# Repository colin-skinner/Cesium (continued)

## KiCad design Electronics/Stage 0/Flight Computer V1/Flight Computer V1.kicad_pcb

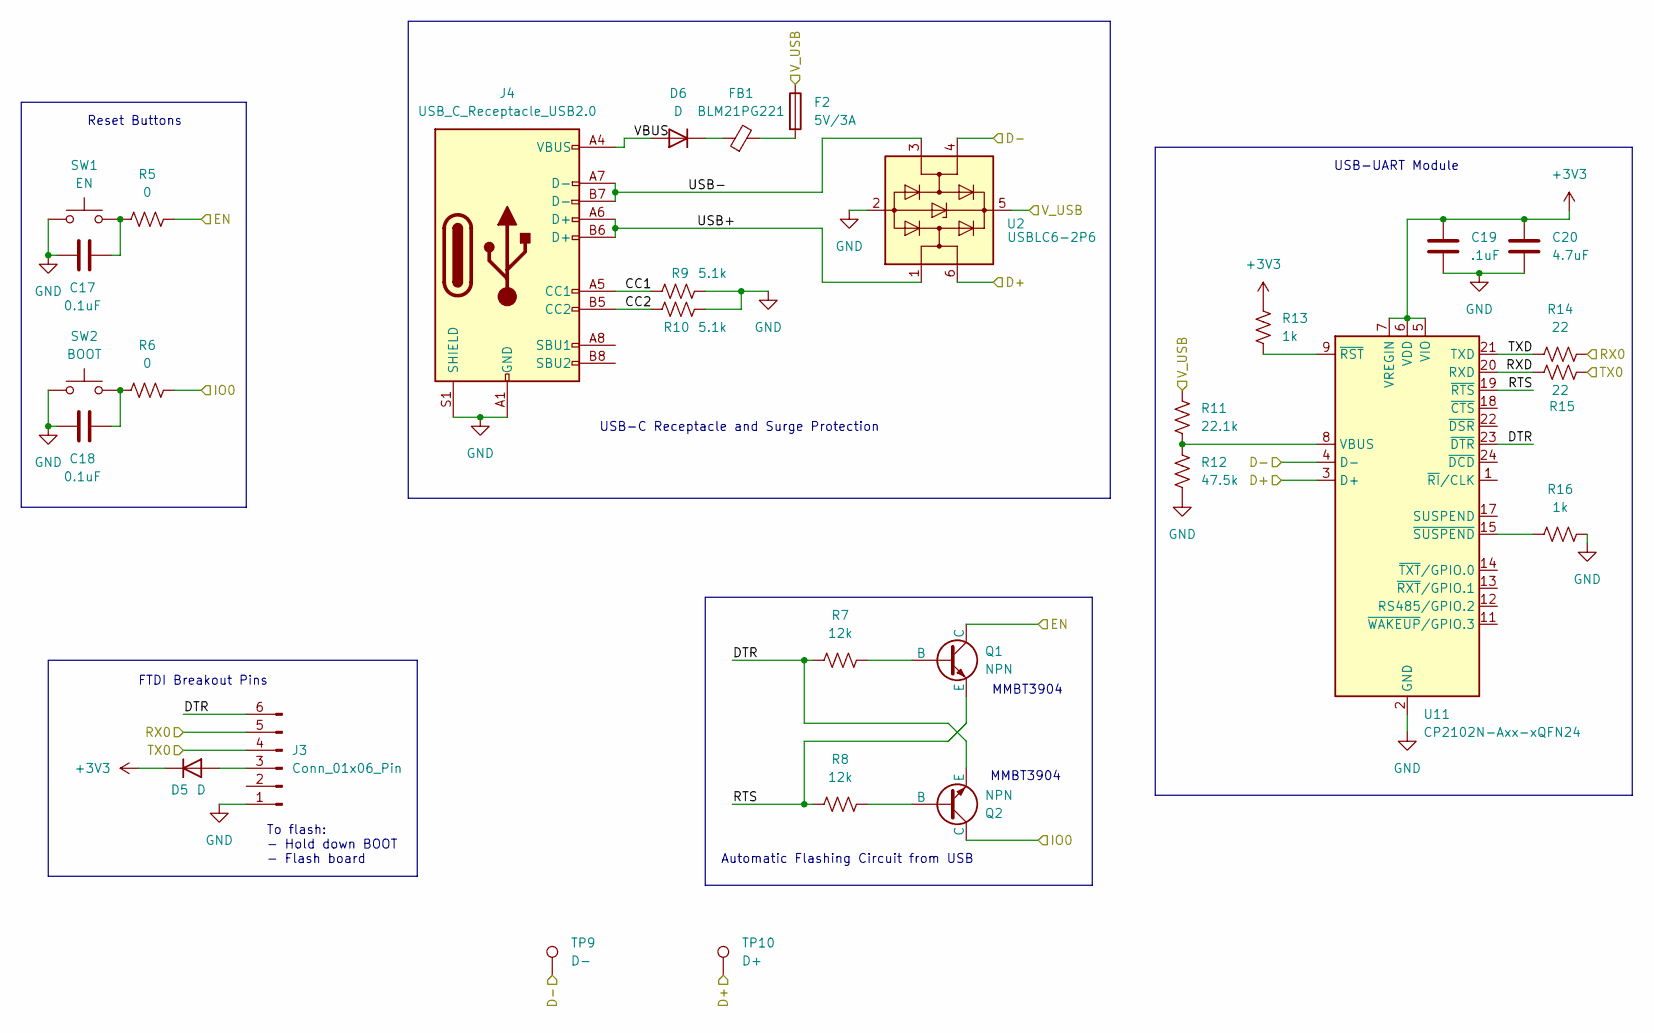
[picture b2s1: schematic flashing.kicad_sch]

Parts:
C17, C18: 0.1uF; C_0603_1608Metric
C19: .1uF; C_0603_1608Metric
C20: 4.7uF; C_0603_1608Metric
D5, D6: D; D_0603_1608Metric
F2: 5V/3A; Fuse_0603_1608Metric
FB1: BLM21PG221; L_0603_1608Metric_Pad1.05x0.95mm_HandSolder
J3: Conn_01x06_Pin; PinSocket_1x06_P2.54mm_Vertical
J4: USB_C_Receptacle_USB2.0; USB_C_Receptacle_HRO_TYPE-C-31-M-12
Q1, Q2: NPN; SOT-23
R5, R6: 0; R_0603_1608Metric
R7, R8: 12k; R_0603_1608Metric
R9, R10: 5.1k; R_0603_1608Metric
R11: 22.1k; R_0603_1608Metric
R12: 47.5k; R_0603_1608Metric
R13, R16: 1k; R_0603_1608Metric
R14, R15: 22; R_0603_1608Metric
SW1: EN; SW_SPST_B3S-1000
SW2: BOOT; SW_SPST_B3S-1000
TP9: D-; PinHeader_1x01_P2.54mm_Vertical
TP10: D+; PinHeader_1x01_P2.54mm_Vertical
U2: USBLC6-2P6; SOT-666
U11: CP2102N-Axx-xQFN24; QFN-24-1EP_4x4mm_P0.5mm_EP2.6x2.6mm

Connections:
+3V3: C19.1, C20.1, D5.1 (K), R13.2, U11.5 (VIO), U11.6 (VDD), U11.7 (VREGIN); also elsewhere on the board
/Flashing/CC1: J4.A5 (CC1), R9.1
/Flashing/CC2: J4.B5 (CC2), R10.1
/Flashing/D+: TP10.1, U2.6 (I/O1), U11.3 (D+); also elsewhere on the board
/Flashing/D-: TP9.1, U2.4 (I/O2), U11.4 (D-); also elsewhere on the board
/Flashing/DTR: J3.6, Q2.3 (E), R7.1, U11.23 (~DTR)
/Flashing/EN: Q1.1 (C), R5.2; also elsewhere on the board
/Flashing/IO0: Q2.1 (C), R6.2; also elsewhere on the board
/Flashing/RTS: Q1.3 (E), R8.1, U11.19 (~RTS)
/Flashing/RX0: J3.5, R14.2; also elsewhere on the board
/Flashing/RXD: R15.1, U11.20 (RXD)
/Flashing/TX0: J3.4, R15.2; also elsewhere on the board
/Flashing/TXD: R14.1, U11.21 (TXD)
/Flashing/USB+: J4.A6 (D+), J4.B6 (D+), U2.1 (I/O1)
/Flashing/USB-: J4.A7 (D-), J4.B7 (D-), U2.3 (I/O2)
/Flashing/VBUS: D6.2 (A), J4.A4 (VBUS), J4.A9 (VBUS), J4.B4 (VBUS), J4.B9 (VBUS)
/Flashing/V_USB: F2.1, R11.1, U2.5 (VBUS); also elsewhere on the board
GND: C17.1, C18.1, C19.2, C20.2, J3.1, J4.A1 (GND), J4.A12 (GND), J4.B1 (GND), J4.B12 (GND), J4.S1 (SHIELD), R9.2, R10.2, R12.2, R16.2, SW1.1, SW2.1, U2.2 (GND), U11.2 (GND), U11.25 (GND); also elsewhere on the board
unnamed: C17.2, R5.1, SW1.2
unnamed: C18.2, R6.1, SW2.2
unnamed: D5.2 (A), J3.3
unnamed: D6.1 (K), FB1.1
unnamed: F2.2, FB1.2
unnamed: Q1.2 (B), R7.2
unnamed: Q2.2 (B), R8.2
unnamed: R11.2, R12.1, U11.8 (VBUS)
unnamed: R13.1, U11.9 (~RST)
unnamed: R16.1, U11.15 (~SUSPEND)

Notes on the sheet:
MMBT3904
USB-C Receptacle and Surge Protection
Reset Buttons
FTDI Breakout Pins
Automatic Flashing Circuit from USB
To flash: - Hold down BOOT - Flash board
USB-UART Module

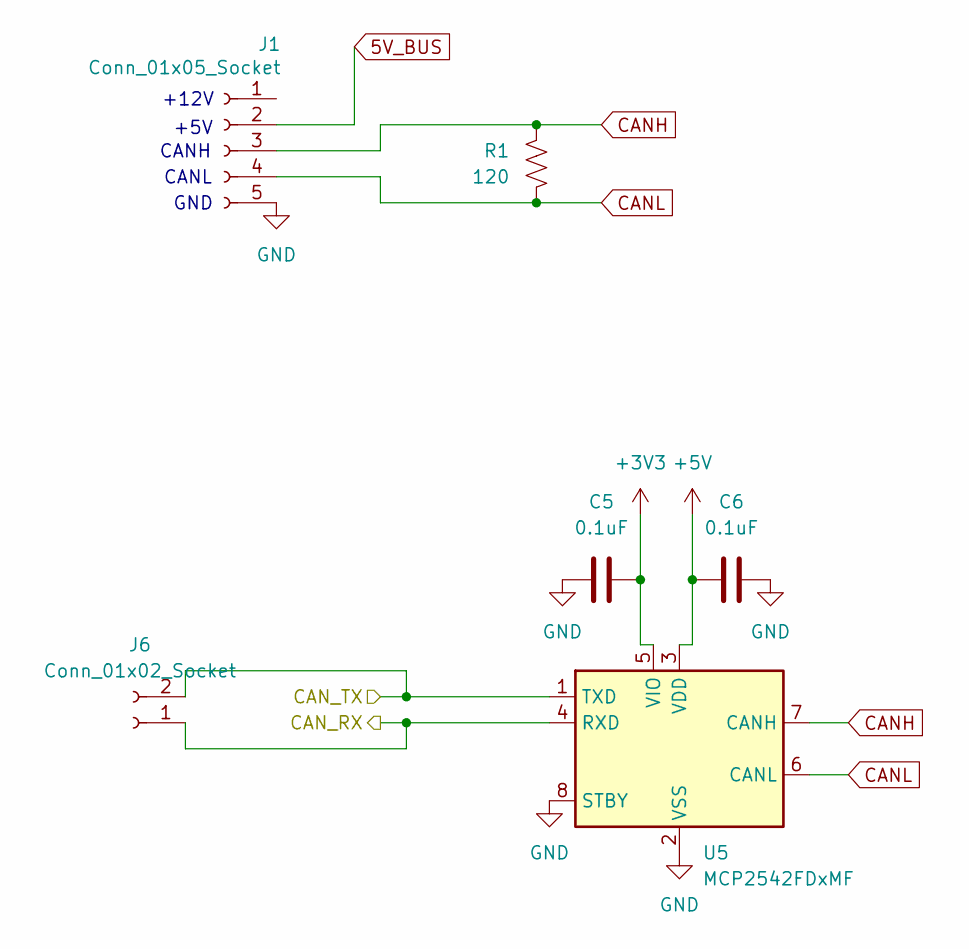
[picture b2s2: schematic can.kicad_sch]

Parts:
C5, C6: 0.1uF; C_0603_1608Metric
J1: Conn_01x05_Socket; PinSocket_1x05_P2.54mm_Vertical
J6: Conn_01x02_Socket; PinSocket_1x02_P2.54mm_Vertical
R1: 120; R_0603_1608Metric
U5: MCP2542FDxMF; DFN-8-1EP_3x3mm_P0.65mm_EP1.55x2.4mm

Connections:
5V_BUS: J1.2; also elsewhere on the board
+3V3: C5.2, U5.5 (VIO); also elsewhere on the board
+5V: C6.1, U5.3 (VDD); also elsewhere on the board
/CAN Bus/CAN_RX: J6.1, U5.4 (RXD); also elsewhere on the board
/CAN Bus/CAN_TX: J6.2, U5.1 (TXD); also elsewhere on the board
CANH: J1.3, R1.1, U5.7 (CANH)
CANL: J1.4, R1.2, U5.6 (CANL)
GND: C5.1, C6.2, J1.5, U5.2 (VSS), U5.8 (STBY), U5.9 (VSS); also elsewhere on the board

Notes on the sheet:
CANH
+5V
+12V
GND
CANL

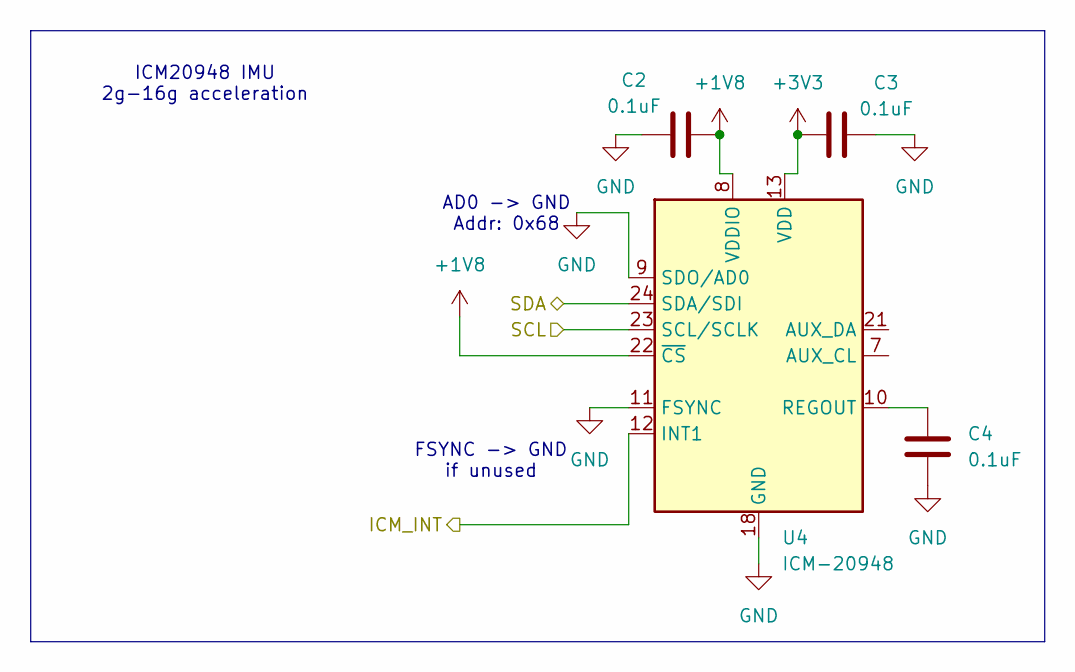
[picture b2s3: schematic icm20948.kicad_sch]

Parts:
C2, C3, C4: 0.1uF; C_0603_1608Metric
U4: ICM-20948; InvenSense_QFN-24_3x3mm_P0.4mm

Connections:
+1V8: C2.2, U4.8 (VDDIO), U4.22 (~CS); also elsewhere on the board
+3V3: C3.1, U4.13 (VDD); also elsewhere on the board
/ADXL375/SCL: U4.23 (SCL/SCLK); also elsewhere on the board
/ADXL375/SDA: U4.24 (SDA/SDI); also elsewhere on the board
/ICM20948 IMU/ICM_INT: U4.12 (INT1); also elsewhere on the board
GND: C2.1, C3.2, C4.2, U4.9 (SDO/AD0), U4.11 (FSYNC), U4.18 (GND), U4.20 (GND); also elsewhere on the board
unnamed: C4.1, U4.10 (REGOUT)

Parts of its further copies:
C25, C26, C27: 0.1uF; C_0603_1608Metric
U12: ICM-20948; InvenSense_QFN-24_3x3mm_P0.4mm

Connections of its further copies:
+1V8: C25.2, U12.8 (VDDIO), U12.22 (~CS); also elsewhere on the board
+3V3: C26.1, U12.13 (VDD); also elsewhere on the board
/ADXL375/SCL: U12.23 (SCL/SCLK); also elsewhere on the board
/ADXL375/SDA: U12.24 (SDA/SDI); also elsewhere on the board
/ICM20948 IMU1/ICM_INT: U12.12 (INT1); also elsewhere on the board
GND: C25.1, C26.2, C27.2, U12.9 (SDO/AD0), U12.11 (FSYNC), U12.18 (GND), U12.20 (GND); also elsewhere on the board
unnamed: C27.1, U12.10 (REGOUT)

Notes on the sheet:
ICM20948 IMU 2g-16g acceleration
FSYNC -> GND if unused
AD0 -> GND Addr: 0x68

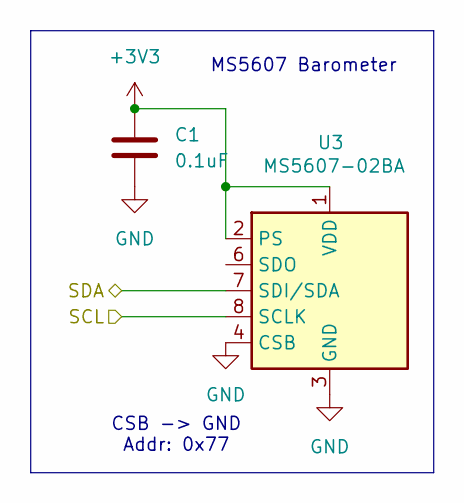
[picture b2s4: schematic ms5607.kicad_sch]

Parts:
C1: 0.1uF; C_0603_1608Metric
U3: MS5607-02BA; LGA-8_3x5mm_P1.25mm

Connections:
+3V3: C1.1, U3.1 (VDD), U3.2 (PS); also elsewhere on the board
/ADXL375/SCL: U3.8 (SCLK); also elsewhere on the board
/ADXL375/SDA: U3.7 (SDI/SDA); also elsewhere on the board
GND: C1.2, U3.3 (GND), U3.4 (CSB), U3.5 (CSB); also elsewhere on the board

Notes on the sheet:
CSB -> GND Addr: 0x77
MS5607 Barometer

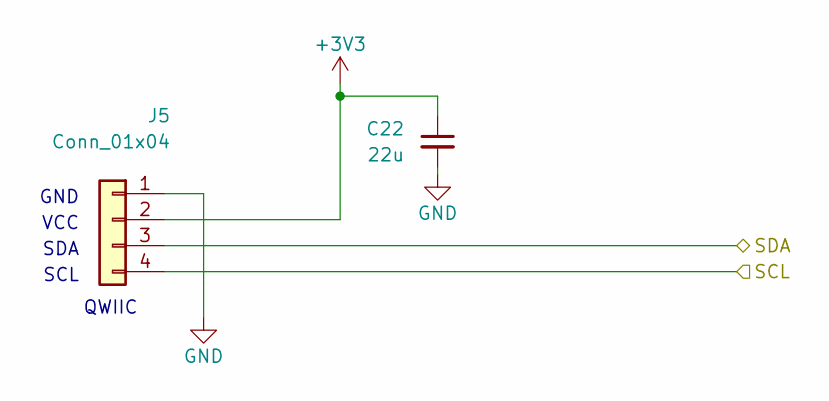
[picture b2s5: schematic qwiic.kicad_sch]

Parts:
C22: 22u; C_0805_2012Metric_Pad1.18x1.45mm_HandSolder
J5: Conn_01x04; JST_SH_SM04B-SRSS-TB_1x04-1MP_P1.00mm_Horizontal

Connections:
+3V3: C22.1, J5.2; also elsewhere on the board
/ADXL375/SCL: J5.3; also elsewhere on the board
/ADXL375/SDA: J5.4; also elsewhere on the board
GND: C22.2, J5.1; also elsewhere on the board

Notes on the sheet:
VCC
SDA
SCL
QWIIC
GND

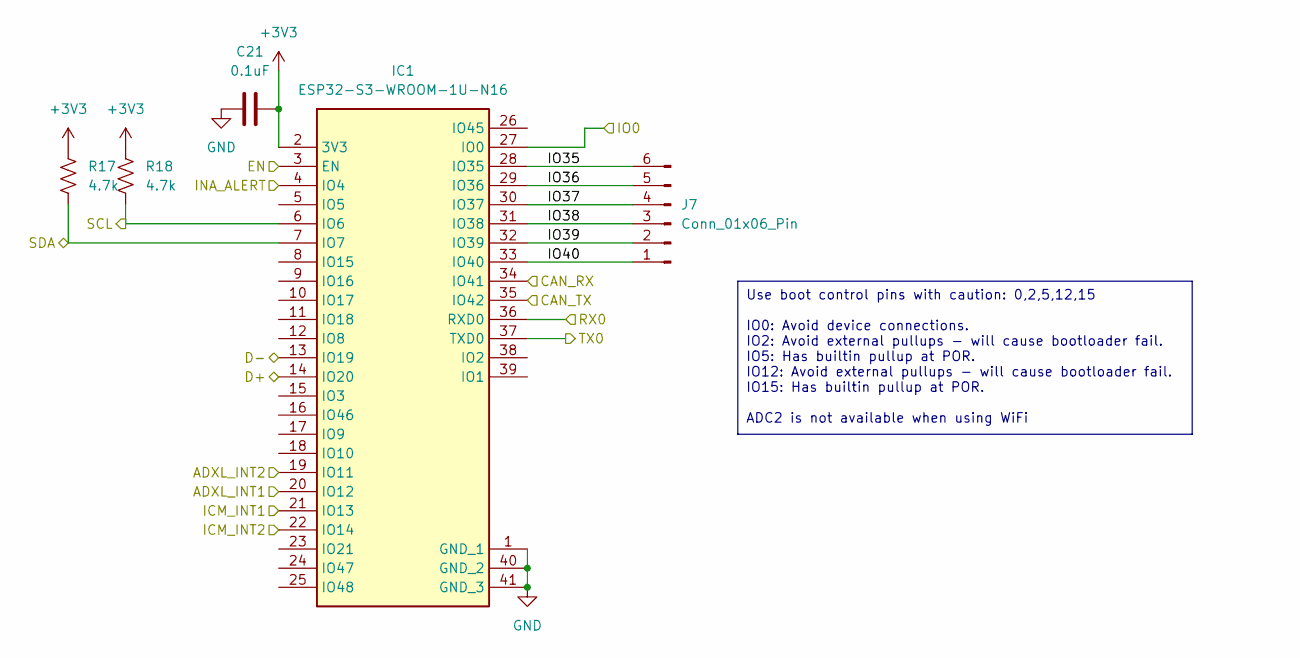
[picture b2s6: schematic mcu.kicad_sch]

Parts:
C21: 0.1uF; C_0603_1608Metric
IC1: ESP32-S3-WROOM-1U-N16; ESP32-S3-WROOM-1U; Mouser Part Number 356-ESP32S3WROM1UN16
J7: Conn_01x06_Pin; PinSocket_1x06_P2.54mm_Vertical
R17, R18: 4.7k; R_0603_1608Metric

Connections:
+3V3: C21.1, IC1.2 (3V3), R17.1, R18.1; also elsewhere on the board
/ADXL375/ADXL_INT1: IC1.20 (IO12); also elsewhere on the board
/ADXL375/ADXL_INT2: IC1.19 (IO11); also elsewhere on the board
/ADXL375/SCL: IC1.6 (IO6), R18.2; also elsewhere on the board
/ADXL375/SDA: IC1.7 (IO7), R17.2; also elsewhere on the board
/CAN Bus/CAN_RX: IC1.35 (IO42); also elsewhere on the board
/CAN Bus/CAN_TX: IC1.34 (IO41); also elsewhere on the board
/Flashing/D+: IC1.14 (IO20); also elsewhere on the board
/Flashing/D-: IC1.13 (IO19); also elsewhere on the board
/Flashing/EN: IC1.3 (EN); also elsewhere on the board
/Flashing/IO0: IC1.27 (IO0); also elsewhere on the board
/Flashing/RX0: IC1.36 (RXD0); also elsewhere on the board
/Flashing/TX0: IC1.37 (TXD0); also elsewhere on the board
/ICM20948 IMU1/ICM_INT: IC1.22 (IO14); also elsewhere on the board
/ICM20948 IMU/ICM_INT: IC1.21 (IO13); also elsewhere on the board
/MCU/INA_ALERT: IC1.4 (IO4); also elsewhere on the board
/MCU/IO35: IC1.28 (IO35), J7.6
/MCU/IO36: IC1.29 (IO36), J7.5
/MCU/IO37: IC1.30 (IO37), J7.4
/MCU/IO38: IC1.31 (IO38), J7.3
/MCU/IO39: IC1.32 (IO39), J7.2
/MCU/IO40: IC1.33 (IO40), J7.1
GND: C21.2, IC1.1 (GND_1), IC1.40 (GND_2), IC1.41 (GND_3); also elsewhere on the board

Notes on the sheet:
Use boot control pins with caution: 0,2,5,12,15 IO0: Avoid device connections. IO2: Avoid external pullups - will cause bootloader fail. IO5: Has builtin pullup at POR. IO12: Avoid external pullups - will cause bootloader fail. IO15: Has builtin pullup at POR. ADC2 is not available when using WiFi

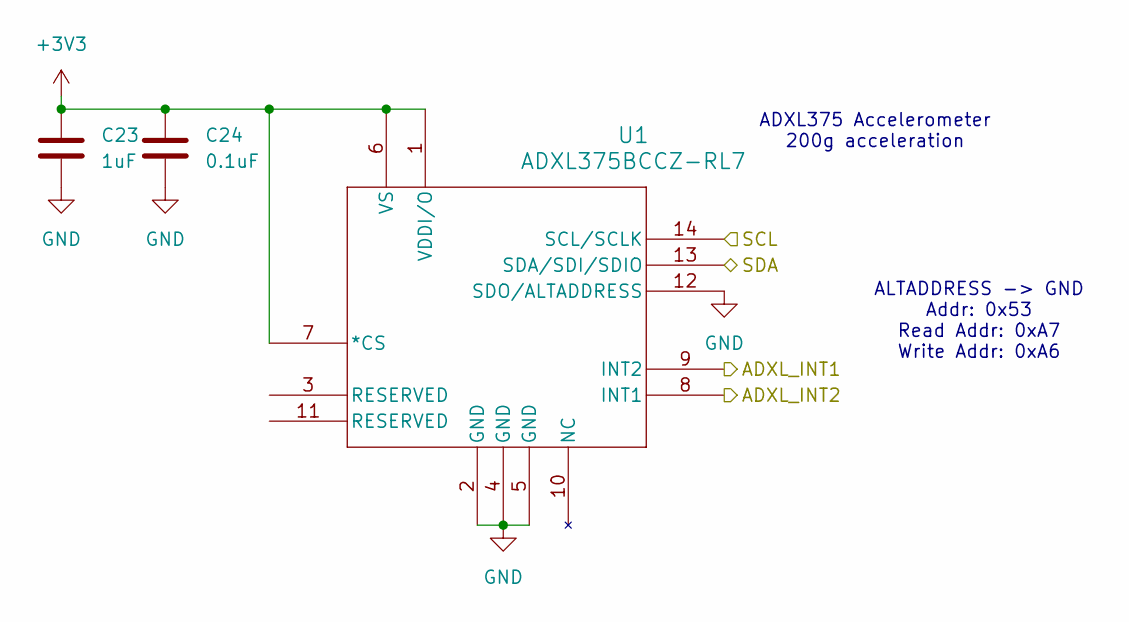
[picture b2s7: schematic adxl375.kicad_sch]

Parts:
C23: 1uF; C_0603_1608Metric
C24: 0.1uF; C_0603_1608Metric
U1: ADXL375BCCZ-RL7; LGA_CC-14-1_ADI

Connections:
+3V3: C23.1, C24.1, U1.1 (VDDI/O), U1.6 (VS), U1.7 (*CS); also elsewhere on the board
/ADXL375/ADXL_INT1: U1.9 (INT2); also elsewhere on the board
/ADXL375/ADXL_INT2: U1.8 (INT1); also elsewhere on the board
/ADXL375/SCL: U1.14 (SCL/SCLK); also elsewhere on the board
/ADXL375/SDA: U1.13 (SDA/SDI/SDIO); also elsewhere on the board
GND: C23.2, C24.2, U1.2 (GND), U1.4 (GND), U1.5 (GND), U1.12 (SDO/ALTADDRESS); also elsewhere on the board

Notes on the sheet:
ADXL375 Accelerometer 200g acceleration
ALTADDRESS -> GND Addr: 0x53 Read Addr: 0xA7 Write Addr: 0xA6

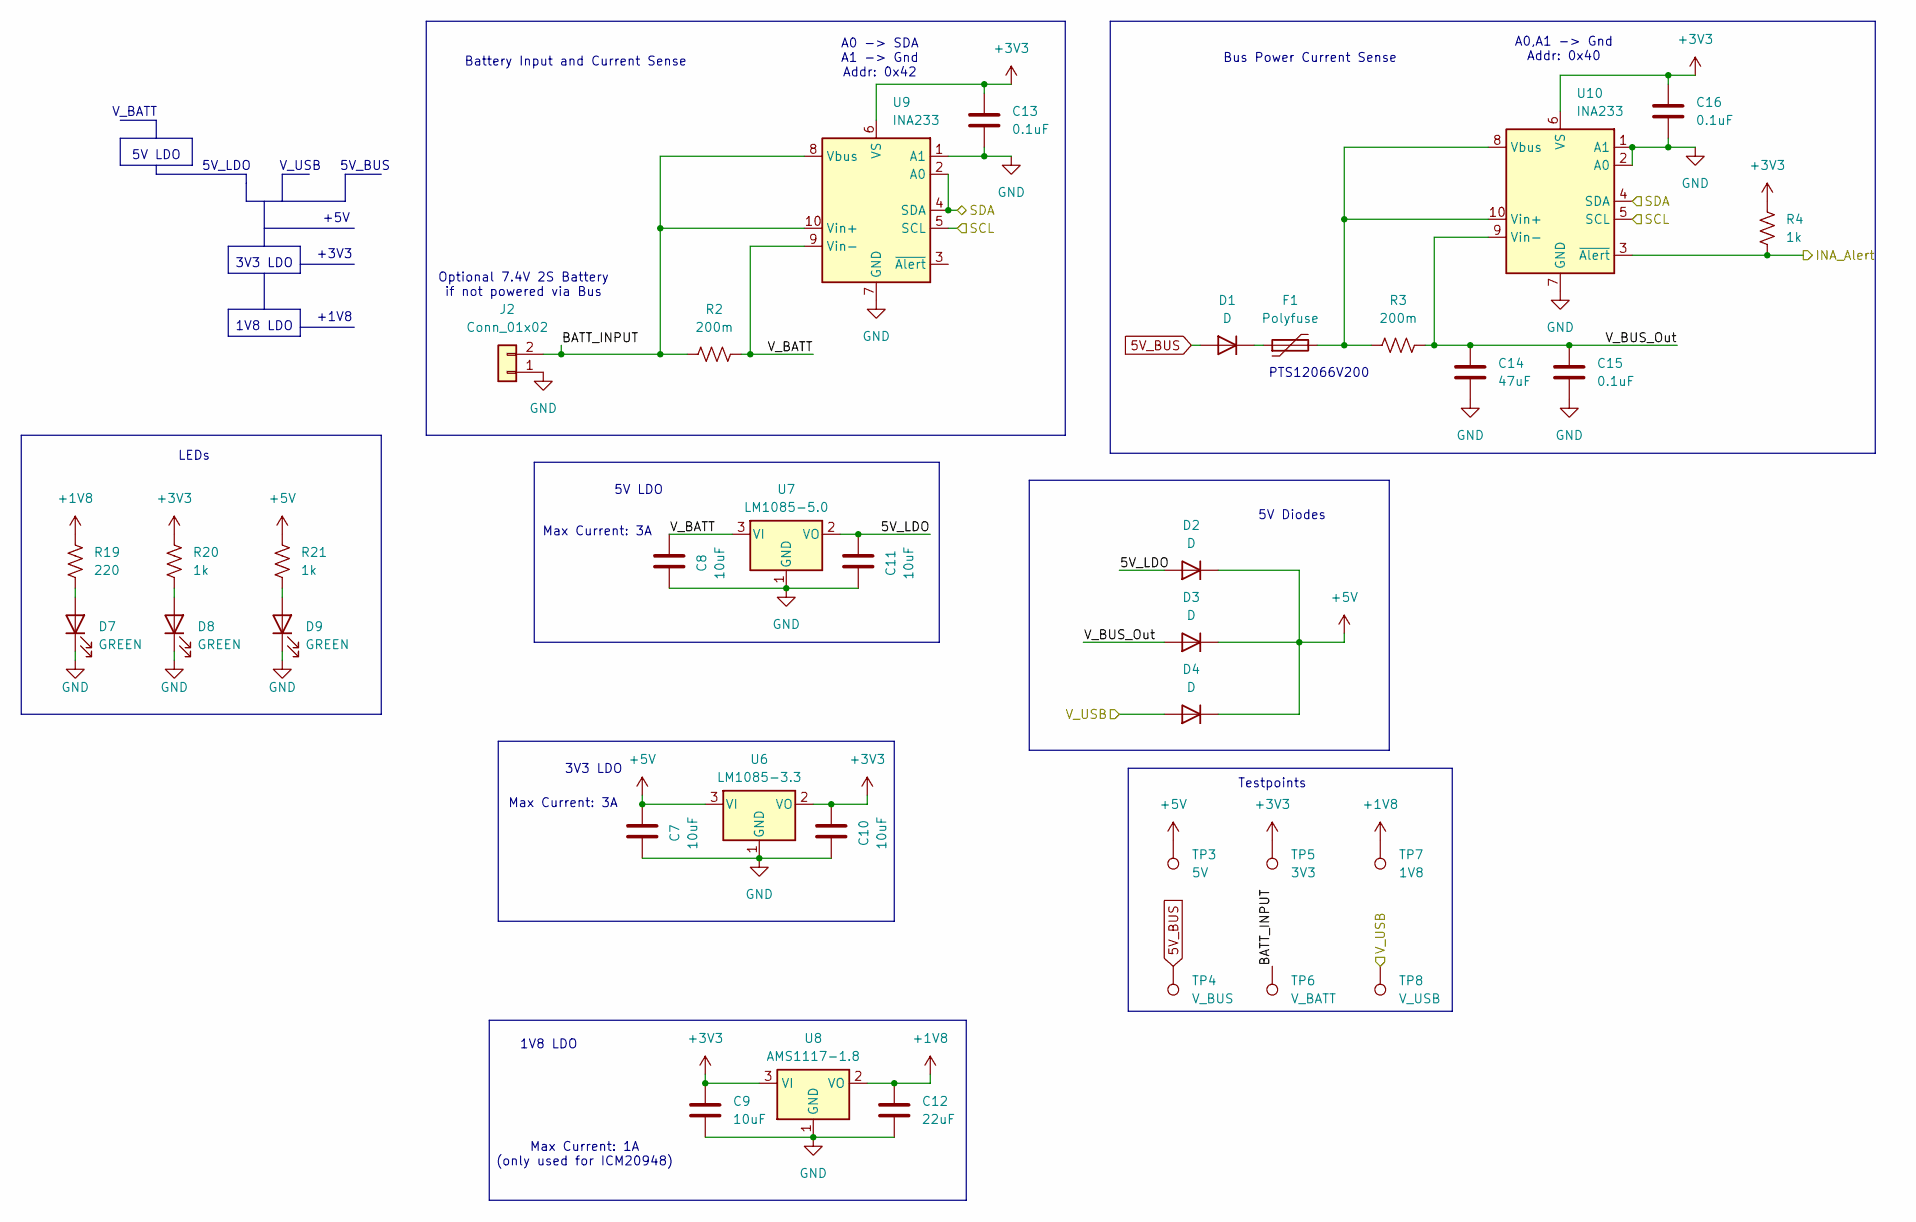
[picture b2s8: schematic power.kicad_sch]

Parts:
C7, C8, C9, C10, C11: 10uF; C_0603_1608Metric
C12: 22uF; C_0603_1608Metric
C13, C15, C16: 0.1uF; C_0603_1608Metric
C14: 47uF; C_0603_1608Metric
D1, D2, D3, D4: D; D_0603_1608Metric
D7, D8, D9: GREEN; LED_0603_1608Metric_Pad1.05x0.95mm_HandSolder
F1: Polyfuse; Fuse_1206_3216Metric
J2: Conn_01x02; AMASS_XT60-M_1x02_P7.20mm_Vertical
R2, R3: 200m; R_0603_1608Metric
R4, R20, R21: 1k; R_0603_1608Metric
R19: 220; R_0603_1608Metric
TP3: 5V; PinHeader_1x01_P2.54mm_Vertical
TP4: V_BUS; PinHeader_1x01_P2.54mm_Vertical
TP5: 3V3; PinHeader_1x01_P2.54mm_Vertical
TP6: V_BATT; PinHeader_1x01_P2.54mm_Vertical
TP7: 1V8; PinHeader_1x01_P2.54mm_Vertical
TP8: V_USB; PinHeader_1x01_P2.54mm_Vertical
U6: LM1085-3.3; TO-263-3_TabPin2
U7: LM1085-5.0; TO-263-3_TabPin2
U8: AMS1117-1.8; SOT-223-3_TabPin2
U9, U10: INA233; VSSOP-10_3x3mm_P0.5mm

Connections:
5V_BUS: D1.2 (A), TP4.1; also elsewhere on the board
+1V8: C12.1, R19.2, TP7.1, U8.2 (VO); also elsewhere on the board
+3V3: C9.1, C10.2, C13.1, C16.1, R4.2, R20.2, TP5.1, U6.2 (VO), U8.3 (VI), U9.6 (VS), U10.6 (VS); also elsewhere on the board
+5V: C7.2, D2.1 (K), D3.1 (K), D4.1 (K), R21.2, TP3.1, U6.3 (VI); also elsewhere on the board
/ADXL375/SCL: U9.5 (SCL), U10.5 (SCL); also elsewhere on the board
/ADXL375/SDA: U9.2 (A0), U9.4 (SDA), U10.4 (SDA); also elsewhere on the board
/Flashing/V_USB: D4.2 (A), TP8.1; also elsewhere on the board
/MCU/INA_ALERT: R4.1, U10.3 (~Alert); also elsewhere on the board
/Power/5V_LDO: C11.2, D2.2 (A), U7.2 (VO)
/Power/BATT_INPUT: J2.2, R2.1, TP6.1, U9.8 (Vbus), U9.10 (Vin+)
/Power/V_BATT: C8.2, R2.2, U7.3 (VI), U9.9 (Vin-)
/Power/V_BUS_Out: C14.1, C15.1, D3.2 (A), R3.2, U10.9 (Vin-)
GND: C7.1, C8.1, C9.2, C10.1, C11.1, C12.2, C13.2, C14.2, C15.2, C16.2, D7.1 (K), D8.1 (K), D9.1 (K), J2.1, U6.1 (GND), U7.1 (GND), U8.1 (GND), U9.1 (A1), U9.7 (GND), U10.1 (A1), U10.2 (A0), U10.7 (GND); also elsewhere on the board
unnamed: D1.1 (K), F1.1
unnamed: D7.2 (A), R19.1
unnamed: D8.2 (A), R20.1
unnamed: D9.2 (A), R21.1
unnamed: F1.2, R3.1, U10.8 (Vbus), U10.10 (Vin+)

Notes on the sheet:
Battery Input and Current Sense
Testpoints
PTS12066V200
5V LDO
Max Current: 3A
LEDs
3V3 LDO
+3V3
Max Current: 1A (only used for ICM20948)
5V_LDO
1V8 LDO
Bus Power Current Sense
A0 -> SDA A1 -> Gnd Addr: 0x42
+1V8
+5V
5V_BUS
V_USB
Optional 7.4V 2S Battery if not powered via Bus
V_BATT
5V Diodes
A0,A1 -> Gnd Addr: 0x40

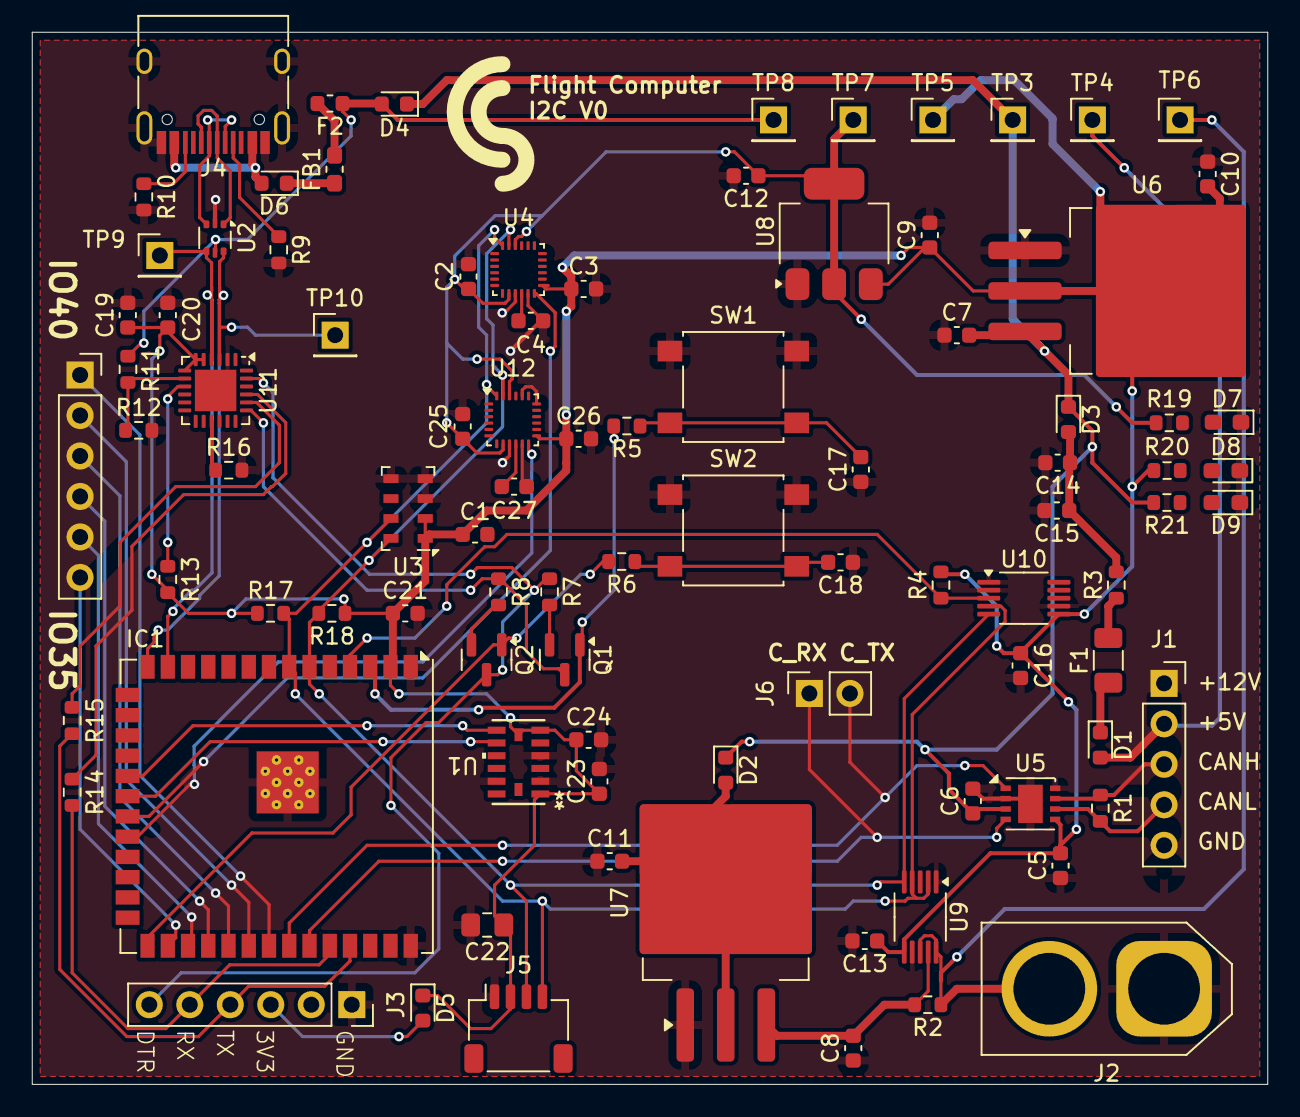
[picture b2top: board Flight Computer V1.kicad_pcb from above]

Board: 2 copper layers, 77.5 x 66.0 mm, 92 parts (0 on the bottom side), 59 nets.

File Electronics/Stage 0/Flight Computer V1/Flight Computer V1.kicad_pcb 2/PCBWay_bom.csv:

Designator,Quantity,Value,Footprint,Package,MPN,DNP,Mount_Type,Description,Sim.Device,Sim.Pins,Height,Mouser Part Number,Mouser Price/Stock,Manufacturer_Name,Sim.Type
"C1, C13, C15, C16, C17, C18, C2, C21, C24, C25, C26, C27, C3, C4, C5, C6",16,0.1uF,C_0603_1608Metric,,,,smt,Unpolarized capacitor,,,,,,,
"C10, C11, C7, C8, C9",5,10uF,C_0603_1608Metric,,,,smt,Unpolarized capacitor,,,,,,,
C12,1,22uF,C_0603_1608Metric,,,,smt,Unpolarized capacitor,,,,,,,
C14,1,47uF,C_0603_1608Metric,,,,smt,Unpolarized capacitor,,,,,,,
C19,1,.1uF,C_0603_1608Metric,,,,smt,Unpolarized capacitor,,,,,,,
C20,1,4.7uF,C_0603_1608Metric,,,,smt,Unpolarized capacitor,,,,,,,
C22,1,22u,C_0805_2012Metric_Pad1.18x1.45mm_HandSolder,,,,smt,,,,,,,,
C23,1,1uF,C_0603_1608Metric,,,,smt,Unpolarized capacitor,,,,,,,
"D1, D2, D3, D4, D5, D6",6,D,D_0603_1608Metric,,,,smt,Diode,D,1=K 2=A,,,,,
"D7, D8, D9",3,GREEN,LED_0603_1608Metric_Pad1.05x0.95mm_HandSolder,,,,smt,,,,,,,,
F1,1,Polyfuse,Fuse_1206_3216Metric,,,,smt,"Resettable fuse, polymeric positive temperature coefficient",,,,,,,
F2,1,5V/3A,Fuse_0603_1608Metric,,,,smt,Fuse,,,,,,,
FB1,1,BLM21PG221,L_0603_1608Metric_Pad1.05x0.95mm_HandSolder,,,,smt,,,,,,,,
IC1,1,ESP32-S3-WROOM-1U-N16,ESP32-S3-WROOM-1U,,ESP32-S3-WROOM-1U-N16,,smt,"Multiprotocol Modules SMD Module, ESP32-S3, 16 MB SPI Flash, IPEX Antenna Connector",,,3.35,356-ESP32S3WROM1UN16,https://www.mouser.co.uk/ProductDetail/Espressif-Systems/ESP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,Espressif Systems,
J1,1,Conn_01x05_Socket,PinSocket_1x05_P2.54mm_Vertical,,,,tht,"Generic connector, single row, 01x05, script generated",,,,,,,
J2,1,Conn_01x02,AMASS_XT60-M_1x02_P7.20mm_Vertical,,,,tht,"Generic connector, single row, 01x02, script generated (kicad-library-utils/schlib/autogen/connector/)",,,,,,,
"J3, J7",2,Conn_01x06_Pin,PinSocket_1x06_P2.54mm_Vertical,,,,tht,"Generic connector, single row, 01x06, script generated",,,,,,,
J4,1,USB_C_Receptacle_USB2.0,USB_C_Receptacle_HRO_TYPE-C-31-M-12,,,,smt,,,,,,,,
J5,1,Conn_01x04,JST_SH_SM04B-SRSS-TB_1x04-1MP_P1.00mm_Horizontal,,,,smt,,,,,,,,
J6,1,Conn_01x02_Socket,PinSocket_1x02_P2.54mm_Vertical,,,,tht,"Generic connector, single row, 01x02, script generated",,,,,,,
"Q1, Q2",2,NPN,SOT-23,,,,smt,"Bipolar transistor symbol for simulation only, substrate tied to the emitter",NPN,1=C 2=B 3=E,,,,,GUMMELPOON
R1,1,120,R_0603_1608Metric,,,,smt,"Resistor, US symbol",,,,,,,
"R10, R9",2,5.1k,R_0603_1608Metric,,,,smt,"Resistor, US symbol",,,,,,,
R11,1,22.1k,R_0603_1608Metric,,,,smt,"Resistor, US symbol",,,,,,,
R12,1,47.5k,R_0603_1608Metric,,,,smt,"Resistor, US symbol",,,,,,,
"R13, R16, R20, R21, R4",5,1k,R_0603_1608Metric,,,,smt,"Resistor, US symbol",,,,,,,
"R14, R15",2,22,R_0603_1608Metric,,,,smt,"Resistor, US symbol",,,,,,,
"R17, R18",2,4.7k,R_0603_1608Metric,,,,smt,"Resistor, US symbol",,,,,,,
R19,1,220,R_0603_1608Metric,,,,smt,"Resistor, US symbol",,,,,,,
"R2, R3",2,200m,R_0603_1608Metric,,,,smt,"Resistor, US symbol",,,,,,,
"R5, R6",2,0,R_0603_1608Metric,,,,smt,"Resistor, US symbol",,,,,,,
"R7, R8",2,12k,R_0603_1608Metric,,,,smt,"Resistor, US symbol",,,,,,,
SW1,1,EN,SW_SPST_B3S-1000,,,,smt,"Push button switch, generic, two pins",,,,,,,
SW2,1,BOOT,SW_SPST_B3S-1000,,,,smt,"Push button switch, generic, two pins",,,,,,,
TP10,1,D+,PinHeader_1x01_P2.54mm_Vertical,,,,tht,test point,,,,,,,
TP3,1,5V,PinHeader_1x01_P2.54mm_Vertical,,,,tht,test point,,,,,,,
TP4,1,V_BUS,PinHeader_1x01_P2.54mm_Vertical,,,,tht,test point,,,,,,,
TP5,1,3V3,PinHeader_1x01_P2.54mm_Vertical,,,,tht,test point,,,,,,,
TP6,1,V_BATT,PinHeader_1x01_P2.54mm_Vertical,,,,tht,test point,,,,,,,
TP7,1,1V8,PinHeader_1x01_P2.54mm_Vertical,,,,tht,test point,,,,,,,
TP8,1,V_USB,PinHeader_1x01_P2.54mm_Vertical,,,,tht,test point,,,,,,,
TP9,1,D-,PinHeader_1x01_P2.54mm_Vertical,,,,tht,test point,,,,,,,
U1,1,ADXL375BCCZ-RL7,LGA_CC-14-1_ADI,,,,smt,,,,,,,,
"U10, U9",2,INA233,VSSOP-10_3x3mm_P0.5mm,,,,smt,"High-Side or Low-Side Measurement, Bi-Directional Current and Power Monitor (0-36V) with I2C, SMBus-, and PMBus-Compatible Interface, VSSOP-10",,,,,,,
U11,1,CP2102N-Axx-xQFN24,QFN-24-1EP_4x4mm_P0.5mm_EP2.6x2.6mm,,,,smt,"USB to UART master bridge, QFN-24",,,,,,,
"U12, U4",2,ICM-20948,InvenSense_QFN-24_3x3mm_P0.4mm,,,,smt,"InvenSense 9-Axis Motion Sensor, Accelerometer, Gyroscope, Compass, I2C/SPI, QFN-24",,,,,,,
U2,1,USBLC6-2P6,SOT-666,,,,smt,,,,,,,,
U3,1,MS5607-02BA,LGA-8_3x5mm_P1.25mm,,,,smt,"Barometric pressure sensor, 20cm resolution, 10 to 1200 mbar, I2C and SPI interface up to 20MHz, LGA-8",,,,,,,
U5,1,MCP2542FDxMF,DFN-8-1EP_3x3mm_P0.65mm_EP1.55x2.4mm,,,,smt,"CAN-FD Transceiver, Wake-Up on CAN activity, 8Mbps, 5V supply, STBY pin, 3x3 DFN-8",,,,,,,
U6,1,LM1085-3.3,TO-263-3_TabPin2,,,,smt,"3A 27V Linear Regulator, Fixed Output 3.3V, TO-220/TO-263",,,,,,,
U7,1,LM1085-5.0,TO-263-3_TabPin2,,,,smt,"3A 25V Linear Regulator, Fixed Output 5.0V, TO-220/TO-263",,,,,,,
U8,1,AMS1117-1.8,SOT-223-3_TabPin2,,,,smt,"1A Low Dropout regulator, positive, 1.8V fixed output, SOT-223",,,,,,,

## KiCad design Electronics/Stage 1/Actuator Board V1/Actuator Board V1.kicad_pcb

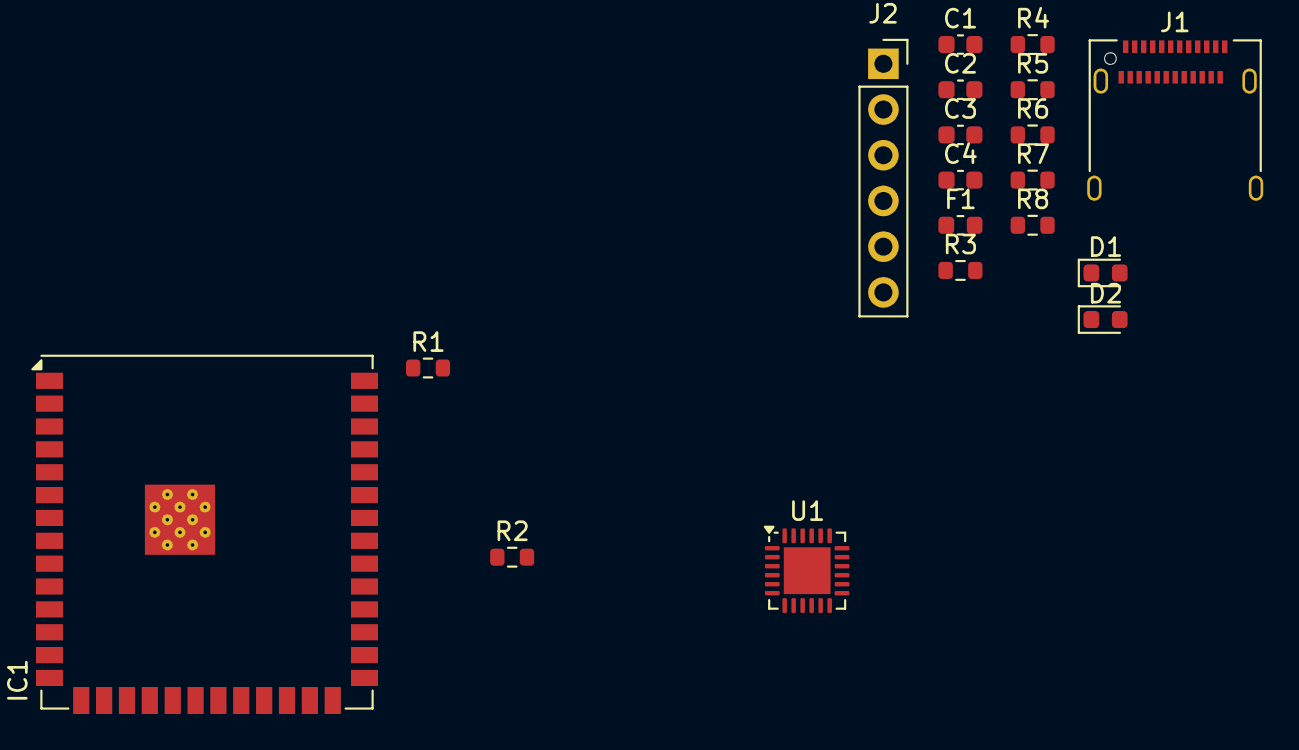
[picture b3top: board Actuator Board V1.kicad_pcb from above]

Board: 2 copper layers, 19 parts (0 on the bottom side), 19 nets, no tracks yet.

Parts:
C1, C3, C4: .1uF; C_0603_1608Metric
C2: 47uF; C_0603_1608Metric
D1, D2: D; D_0603_1608Metric
F1: 5V/3A; Fuse_0603_1608Metric
IC1: ESP32-S3-WROOM-1U-N16; ESP32-S3-WROOM-1U
J1: USB_C_Receptacle_USB2.0_14P; USB_C_Receptacle_Amphenol_12401610E4-2A
J2: Conn_01x06_Pin; PinSocket_1x06_P2.54mm_Vertical
R1, R2: 0; R_0603_1608Metric
R3, R4: 1k; R_0603_1608Metric
R5, R6: 5.1k; R_0603_1608Metric
R7: 47.5k; R_0603_1608Metric
R8: 22.1k; R_0603_1608Metric
U1: CP2102N-Axx-xQFN24; QFN-24-1EP_4x4mm_P0.5mm_EP2.6x2.6mm

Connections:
+3.3V: D2.1 (K), IC1.2 (3V3)
+3V3: C1.1, C2.1, R3.2, U1.5 (VIO), U1.6 (VDD), U1.7 (VREGIN)
/CC1: J1.A5 (CC1), R5.1
/CC2: J1.B5 (CC2), R6.1
/D+: J1.A7 (D-), J1.B7 (D-), U1.3 (D+)
/D-: J1.A6 (D+), J1.B6 (D+), U1.4 (D-)
/DTR: J2.6, U1.23 (~DTR)
/RX0: IC1.36 (RXD0), J2.5, R1.1
/RXD: R2.2, U1.20 (RXD)
/TX0: C3.1, IC1.37 (TXD0), J2.4, R2.1
/TXD: C4.1, R1.2, U1.21 (TXD)
GND: C1.2, C2.2, C3.2, C4.2, IC1.1 (GND_1), IC1.40 (GND_2), IC1.41 (GND_3), J1.A1 (GND), J1.A12 (GND), J1.B1 (GND), J1.B12 (GND), J1.S1 (SHIELD), J2.1, R4.2, R5.2, R6.2, R8.2, U1.2 (GND), U1.25 (GND)
unnamed: D1.2 (A), J1.A4 (VBUS), J1.A9 (VBUS), J1.B4 (VBUS), J1.B9 (VBUS)
unnamed: D1.1 (K), F1.2
unnamed: D2.2 (A), J2.3
unnamed: R7.2, R8.1, U1.8 (VBUS)
unnamed: R3.1, U1.9 (~RST)
unnamed: R4.1, U1.15 (~SUSPEND)
V_USB: F1.1, R7.1

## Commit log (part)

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2024-12-10 Update .gitignore for Python
2024-12-10 Added planning markdowns
2024-12-31 First commit of PlatformIO Code
2024-12-31 README Stage 0 update
2025-01-01 DS3232RTC library
2025-01-01 Telemetry Plan
2025-01-02 PyCommander working command schema
2025-01-02 Telemetry Schema
2025-01-02 esp32 Filesystem and timestamps
2025-01-03 BasePacket with tests, and some minor fixes to headers. Also an actual testing framework.
2025-01-03 Python BasePacket fixes from c++ unit tests
2025-01-03 Working test with decoding on ESP32
2025-01-03 Serial comms class
2025-01-04 Large routing commit
2025-01-04 Unit testing shenanigans
2025-01-11 COBS python
2025-01-12 Jump Clock Working
2025-01-12 More Clock functionality
2025-01-21 Changed location of tasks
2025-01-21 Updated packet schema
2025-01-21 Packet filename changes for #include
2025-01-21 Sensor Bases and Filesystem with Tests
2025-01-21 misc. changes
2025-01-21 Test Rocket Board
2025-01-22 Math and testing, sensor bases and testing
2025-01-27 Laundry list of things - More sensors - IMU packets - Config JSON
2025-01-28 IMU code and some sensor bases
2025-01-29 BMI323, MS5607, and ICM20948 all work together now
2025-01-31 Random
2025-02-03 Filesystem work, and still can't figure out why BMP won't read
2025-02-19 more microcontroller
2025-05-20 Random MicrocontrollerCode additions
2025-05-20 Planning refactor
